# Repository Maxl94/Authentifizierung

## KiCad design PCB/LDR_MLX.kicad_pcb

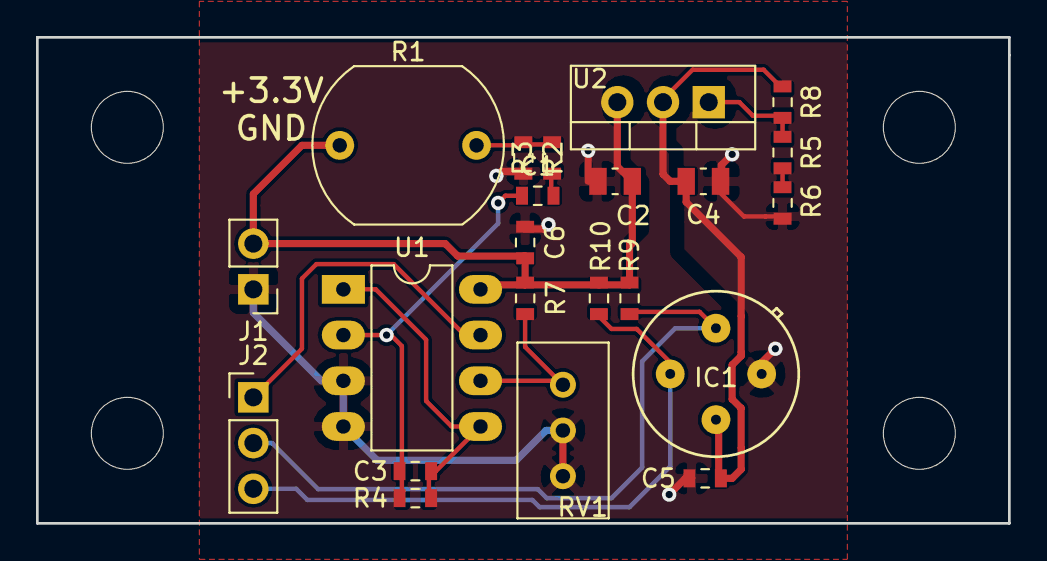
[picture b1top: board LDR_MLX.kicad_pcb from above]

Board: 2 copper layers, 54.0 x 27.0 mm, 22 parts (0 on the bottom side), 13 nets.

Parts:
C1, C5, C6: 100n; C_0603_1608Metric
C2, C4: 1u; C_0805_2012Metric
C3: 100p; C_0603_1608Metric
IC1: MLX90621
J1: Conn_01x02; PinHeader_1x02_P2.54mm_Vertical
J2: Conn_01x03; PinHeader_1x03_P2.54mm_Vertical
R1: R_PHOTO; Resistor_LDR_10x8.5_RM7.6
R2: 10k; R_0603_1608Metric
R3: 1k; R_0603_1608Metric
R4, R7: 100k; R_0603_1608Metric
R5: Behelfswiderstand; R_0603_1608Metric
R6: 130, 390, 510; R_0603_1608Metric
R8: 120, 360, 470; R_0603_1608Metric
R9, R10: 4,7k; R_0603_1608Metric
RV1: 1k; Potentiometer_Bourns_3296W_Vertical
U1: LM2904; DIP-8_W7.62mm_LongPads
U2: LM317_3PinPackage; TO-220-3_Vertical

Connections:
+3V3: C2.2, C6.2, J1.2, R1.1, R7.2, R9.2, R10.2, U1.8, U2.3
/+2.6V: C4.2, C5.2, IC1.3, R8.2, U2.2
/I2C_SCL: IC1.1, J2.2, R9.1
/I2C_SDA: IC1.2, J2.3, R10.1
/LIGHT_DET: J2.1, U1.7
GND: C2.1, C4.1, C5.1, C6.1, IC1.4, J1.1, R2.2, R6.1, RV1.2, RV1.3, U1.3, U1.4
unnamed: C1.1, C3.2, R4.2, U1.2
unnamed: C1.2, R3.1
unnamed: C3.1, R4.1, U1.1, U1.5
unnamed: R1.2, R2.1, R3.2
unnamed: R5.1, R6.2
unnamed: R5.2, R8.1, U2.1
unnamed: R7.1, RV1.1, U1.6

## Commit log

2018-01-08 Init
2018-01-10 Ansteuerung GPS Modul per UART
2018-01-10 Webserver Addes Update, Create, Delete Mode, Bugfiexes Modes
2018-01-10 Added button for stopping alarm, small bugfiex in views
2018-01-10 GPS aufgeräumt, LDR hinzugefügt
2018-01-15 Thermosensor und Auswertung hinzugefügt, IP Addr geg. anpassen
2018-01-16 Addes Michis Zeug und Videos
2018-01-16 Added Video support
2018-01-16 chore: remove unused sensors
2018-01-16 add:add utility files
2018-01-16 fix: change dependency, change file directory
2018-01-16 chore: add vscode to ignore file
2018-01-16 chore: remove vscode dir
2018-01-16 chore: remove __pycache__
2018-01-16 chore: remove .idea from utilities
2018-01-16 chore: remove .iml file
2018-01-16 Added font
2018-01-16 Updatet Settings
2018-01-16 Added: BNO055 9dof sensor
2018-01-16 chore: change hm dir location
2018-01-16 feat: add gyro connection
2018-01-16 fix: spaces and tabs mixed
2018-01-16 chore: add logs for config
2018-01-16 Change start mode
2018-01-16 fix: use start alarm not stop alarm
2018-01-16 fix: using same variable names as django for sensors
2018-01-16 fix: add better print comment
2018-01-16 Debug
2018-01-16 chore: add better debug output
2018-01-16 Pfad angepasst
2018-01-16 Added stop_alarm
2018-01-16 feat: add light sensor
2018-01-16 Added start sensors ond start server
2018-01-16 Bugfix
2018-01-16 fix: doesnt wait for alarm duration if stopped by gui earlier
2018-01-16 Bugfix switch (hoffentlich)
2018-01-16 fix: add init for mixer, renamed vars, used native busy method
2018-01-16 Added: start script for django server
2018-01-16 fix: removed unimplemented method
2018-01-16 LDR Update
2018-01-16 Bugfis switches
2018-01-16 Repaces switch with checkbox
2018-01-16 feat: add ir sensoric
2018-01-16 fix: correct import motion modul for ir
2018-01-16 Bugfix checkbox, hässlich aber geht
2018-01-16 Text rechts
2018-01-16 IR Modul läuft irgendwie
2018-01-20 added: template for paper
2018-01-20 removed copyright space
2018-01-20 Added: Einleitung
2018-01-20 Added: Beschleunigungssensor
2018-01-20 Added: Plattform
2018-01-20 Einleitung umformuliert
2018-01-20 Added: Elektronisches Schloss
2018-01-20 added: Fazit
2018-01-20 fix: Achsenbeschriftung bei Akzelerogramm vertauscht
2018-01-20 Klarstellung was ein Alarm ist
2018-01-21 Text: IR Sensor hinzugefügt
2018-01-21 IR Sensor falsche Datei hinzugefügt
2018-01-23 Sirene Anfang weggeschnitten
2018-01-23 Desgine improvments, Bugfixes
2018-01-23 Schnellerer Abfragezyklus der Sensoren
2018-01-23 Added Savezones
2018-01-23 feat: add dummy for gps implementation
2018-01-23 Added savezones, bugfixes profiles
2018-01-23 feat: add safe zone dummies and gps diff control
2018-01-23 fix: use libary for geo calculations instead of approximation
2018-01-23 Smaller Bugfixes
2018-01-23 feat: implementation for safe zone check
2018-01-23 chore: use higher threshold for gps, add used units in comments
2018-01-23 feat: add implementation to gps_modul
2018-01-23 chore: updat var names to new model names
2018-01-25 HW: Kartenleser (NFC?) hinzugefügt. Kleines Beispiel am Ende
2018-02-03 chore: fix errors in some comments
2018-02-03 feat: add db_rdy_flag as parameter
2018-02-03 Bugfixes Server, added dummy for savezones, fix database
2018-02-03 Bugfix ir sensor
2018-02-03 SyntaxError fix
2018-02-03 Added location
2018-02-03 Added get location
2018-02-03 Addes location js
2018-02-03 Location js
2018-02-03 Added GPS
2018-02-03 Bugfix safezones
2018-02-03 Permant GPS
2018-02-03 Bugfix saving
2018-02-03 Fix Coordinate
2018-02-03 Bugfix gps
2018-02-03 Fix db
2018-02-03 chore: add madness slide
2018-02-03 New GPS Support
2018-02-03 Bugfux
2018-02-03 Removed "check_save_zones"
2018-02-03 Only saving gps data if changed
2018-02-03 Bugfix Coordinates not showing up
2018-02-03 Removed print
2018-02-03 Added Current Location to update
2018-02-03 Removed "Current Location" Entry from overview
2018-02-03 Button left
2018-02-03 Changed label of radius
2018-02-03 Changed labels
2018-02-03 Video support
2018-02-03 Video bugfix
2018-02-03 Bugfix video
2018-02-03 Test2
2018-02-03 Webm support
2018-02-03 Test Video
2018-02-03 Webm
2018-02-03 Flask
2018-02-03 Fixed images size
2018-02-03 Fixed size
2018-02-03 Added NFC support
2018-02-03 Nontype error IR
2018-02-03 Spelling mistake
2018-02-03 Alle Features integriert, zum Testen freigegeben
2018-02-03 Kleinere Aenderungen, Alarm geht automatisch aus wenn Profil gewechselt wird, Datenbank default angepasst
2018-02-04 Poster: Kopfzeile
2018-02-04 Poster finalisiert
2018-02-04 Poster: Typos repariert
2018-02-05 Platine hinzugefügt
2018-02-05 BNO Werte angepasst, Motion Detection History Background angepasst und Request pro Zeit verringert
2018-02-05 Settings: Alle Hosts erlauben Datenbank: Default Werte geändert
2018-02-05 Captive Portal Funktion hinzugefügt: Alle Request ohne bekannte URL werden nun per 302 auf die Loginseite weitergeleitet. Problem ist das die URL RegExe alle mit / enden (z.B. settings/create/) aber 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
2018-02-05 Added LED and alarmstop
2018-02-06 Erneut in richtige Pfade geändert
2018-02-18 Umfragenergebnisse hinzugefügt
